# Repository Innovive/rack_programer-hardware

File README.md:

# rack_programer-hardware
Hardware tool for continuous integration and engineering testing for 3.5 racks

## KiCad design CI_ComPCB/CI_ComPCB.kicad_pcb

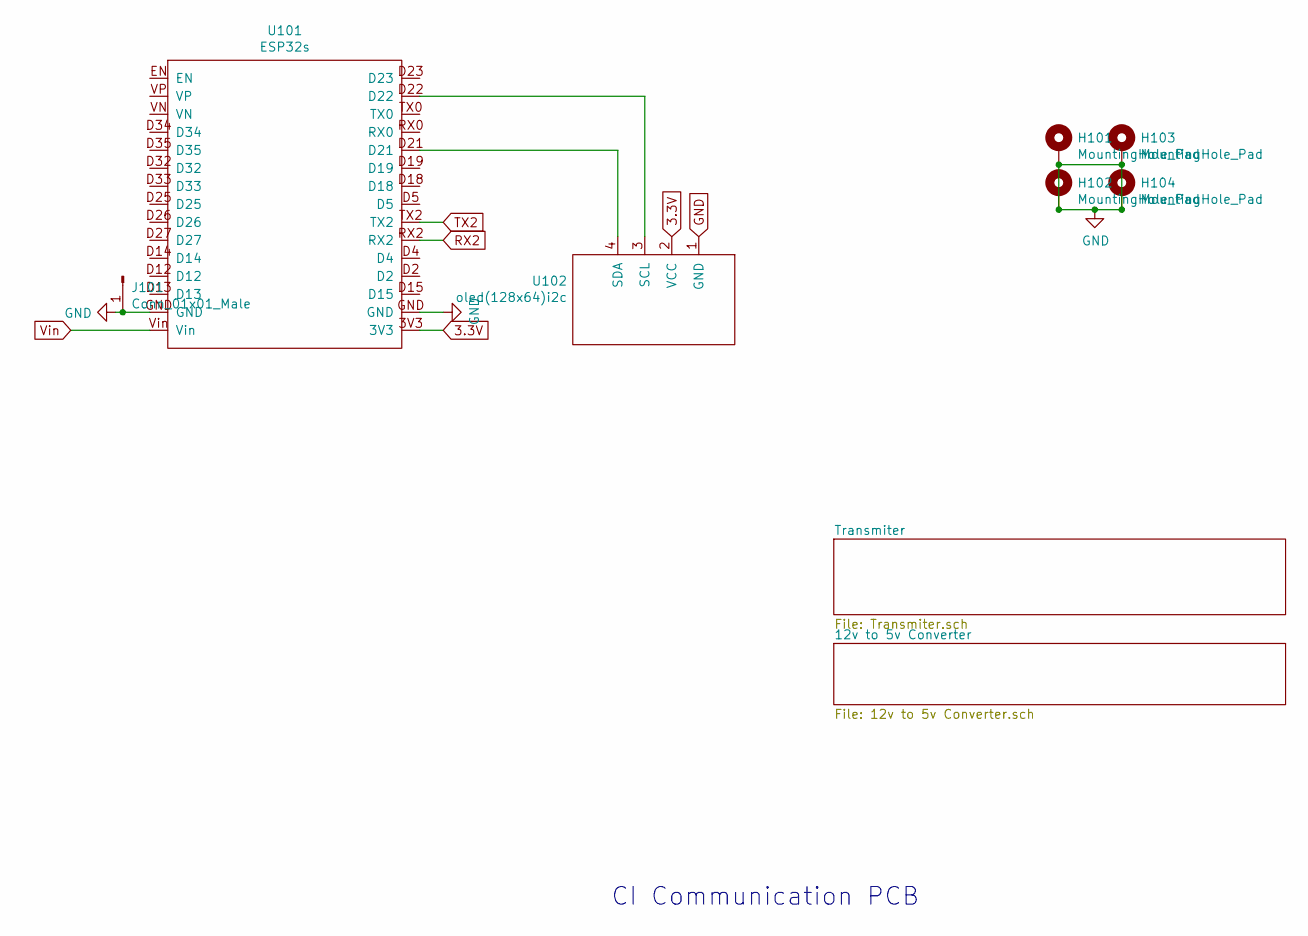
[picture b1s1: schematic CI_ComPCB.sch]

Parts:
H101, H102, H103, H104: MountingHole_Pad; MountingHole_3.2mm_M3_ISO7380_Pad_TopBottom
J101: Conn_01x01_Male; PinHeader_1x01_P2.54mm_Vertical
U101: ESP32s
U102: oled(128x64)i2c

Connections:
3.3V: U101.3V3, U102.2 (VCC); also elsewhere on the board
GND: H101.1, H102.1, H103.1, H104.1, J101.1, U101.GND, U102.1 (GND); also elsewhere on the board
unnamed: U101.D21, U102.4 (SDA)
unnamed: U101.D22, U102.3 (SCL)
RX2: U101.RX2; also elsewhere on the board
TX2: U101.TX2; also elsewhere on the board
Vin: U101.Vin; also elsewhere on the board

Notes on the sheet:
CI Communication PCB

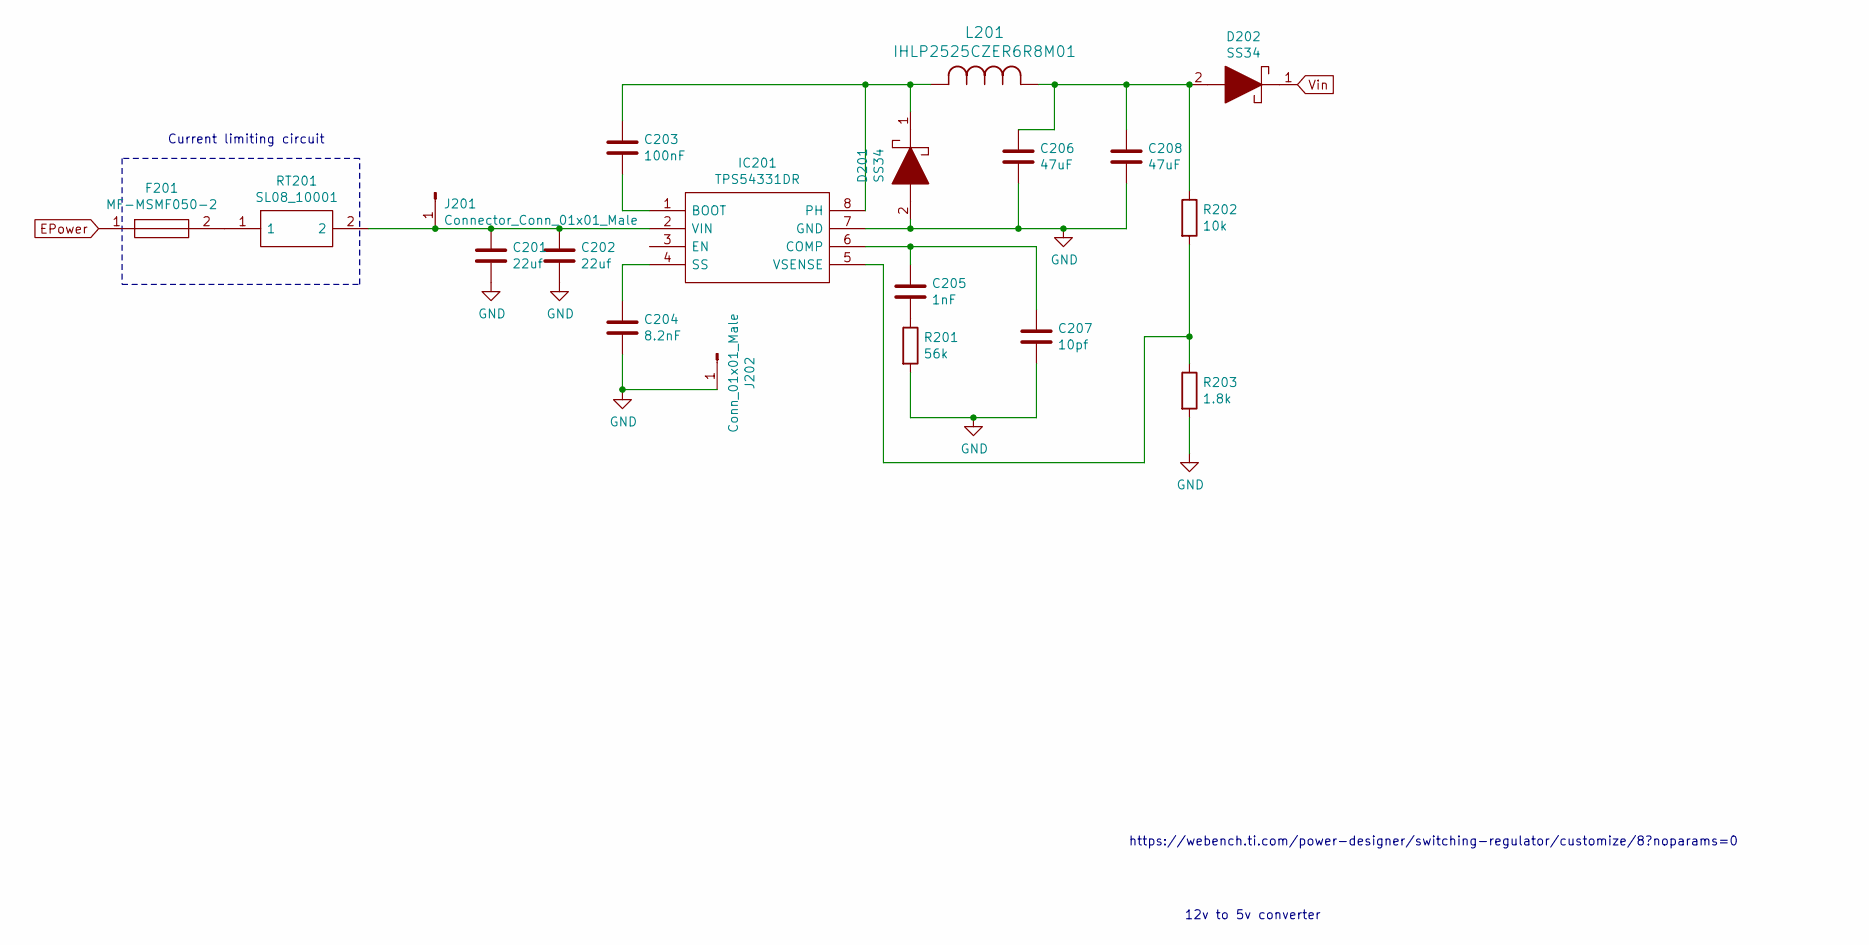
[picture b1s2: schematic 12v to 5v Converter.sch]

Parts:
C201, C202: 22uf; C_1206_3216Metric
C203: 100nF; C_0805_2012Metric
C204: 8.2nF; C_0603_1608Metric; JLCPCB C1032
C205: 1nF; C_0805_2012Metric
C206, C208: 47uF; C_0805_2012Metric
C207: 10pf; C_0805_2012Metric
D201, D202: SS34; DO-214AC; Mouser Part Number 512-SS34
F201: MF-MSMF050-2; FUSC4632X85N; Mouser Part Number 652-MF-MSMF050-2
IC201: TPS54331DR; SOIC127P600X175-8N; Mouser Part Number 595-TPS54331DR
J201: Connector_Conn_01x01_Male; PinHeader_1x01_P2.54mm_Vertical
J202: Conn_01x01_Male; PinHeader_1x01_P2.54mm_Vertical
L201: IHLP2525CZER6R8M01
R201: 56k; R_0805_2012Metric
R202: 10k; R_0805_2012Metric
R203: 1.8k; R_0805_2012Metric
RT201: SL08_10001; SL0810001; Mouser Part Number 995-SL0810001

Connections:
EPower: F201.1; also elsewhere on the board
GND: C201.2, C202.2, C204.2, C206.2, C207.2, C208.2, D201.2, IC201.7 (GND), J202.1, R201.2, R203.2; also elsewhere on the board
unnamed: C201.1, C202.1, IC201.2 (VIN), J201.1, RT201.2
unnamed: C203.1, D201.1, IC201.8 (PH), L201.2
unnamed: C203.2, IC201.1 (BOOT)
unnamed: C204.1, IC201.4 (SS)
unnamed: C205.1, C207.1, IC201.6 (COMP)
unnamed: C205.2, R201.1
unnamed: C206.1, C208.1, D202.2, L201.1, R202.1
unnamed: F201.2, RT201.1
unnamed: IC201.5 (VSENSE), R202.2, R203.1
Vin: D202.1; also elsewhere on the board

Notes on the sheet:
12v to 5v converter
https://webench.ti.com/power-designer/switching-regulator/customize/8?noparams=0
Current limiting circuit

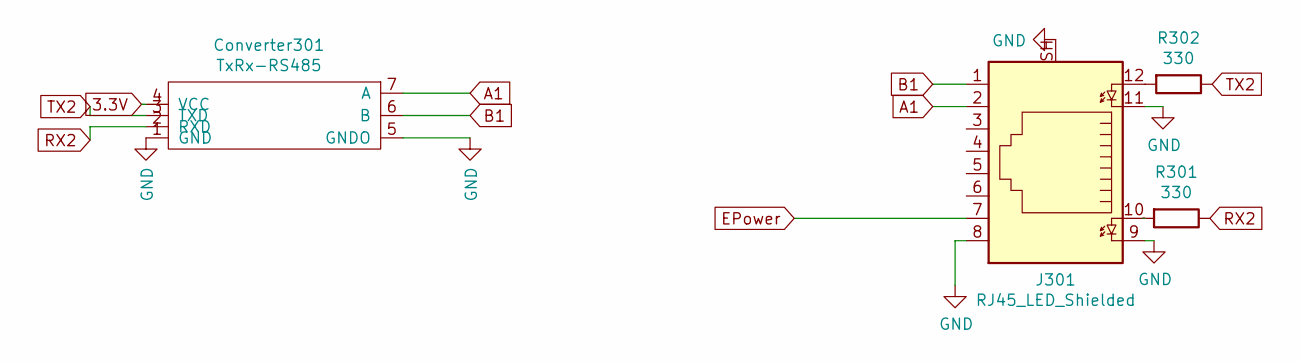
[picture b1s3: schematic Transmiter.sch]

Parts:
Converter301: TxRx-RS485; TXRX-AB
J301: RJ45_LED_Shielded; RJ45_Amphenol_RJHSE538X
R301, R302: 330; R_0805_2012Metric

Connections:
3.3V: Converter301.4 (VCC); also elsewhere on the board
A1: Converter301.7 (A), J301.2
B1: Converter301.6 (B), J301.1
EPower: J301.7; also elsewhere on the board
GND: Converter301.1 (GND), Converter301.5 (GNDO), J301.8, J301.9, J301.11, J301.SH; also elsewhere on the board
unnamed: J301.10, R301.2
unnamed: J301.12, R302.2
RX2: Converter301.2 (RXD), R301.1; also elsewhere on the board
TX2: Converter301.3 (TXD), R302.1; also elsewhere on the board

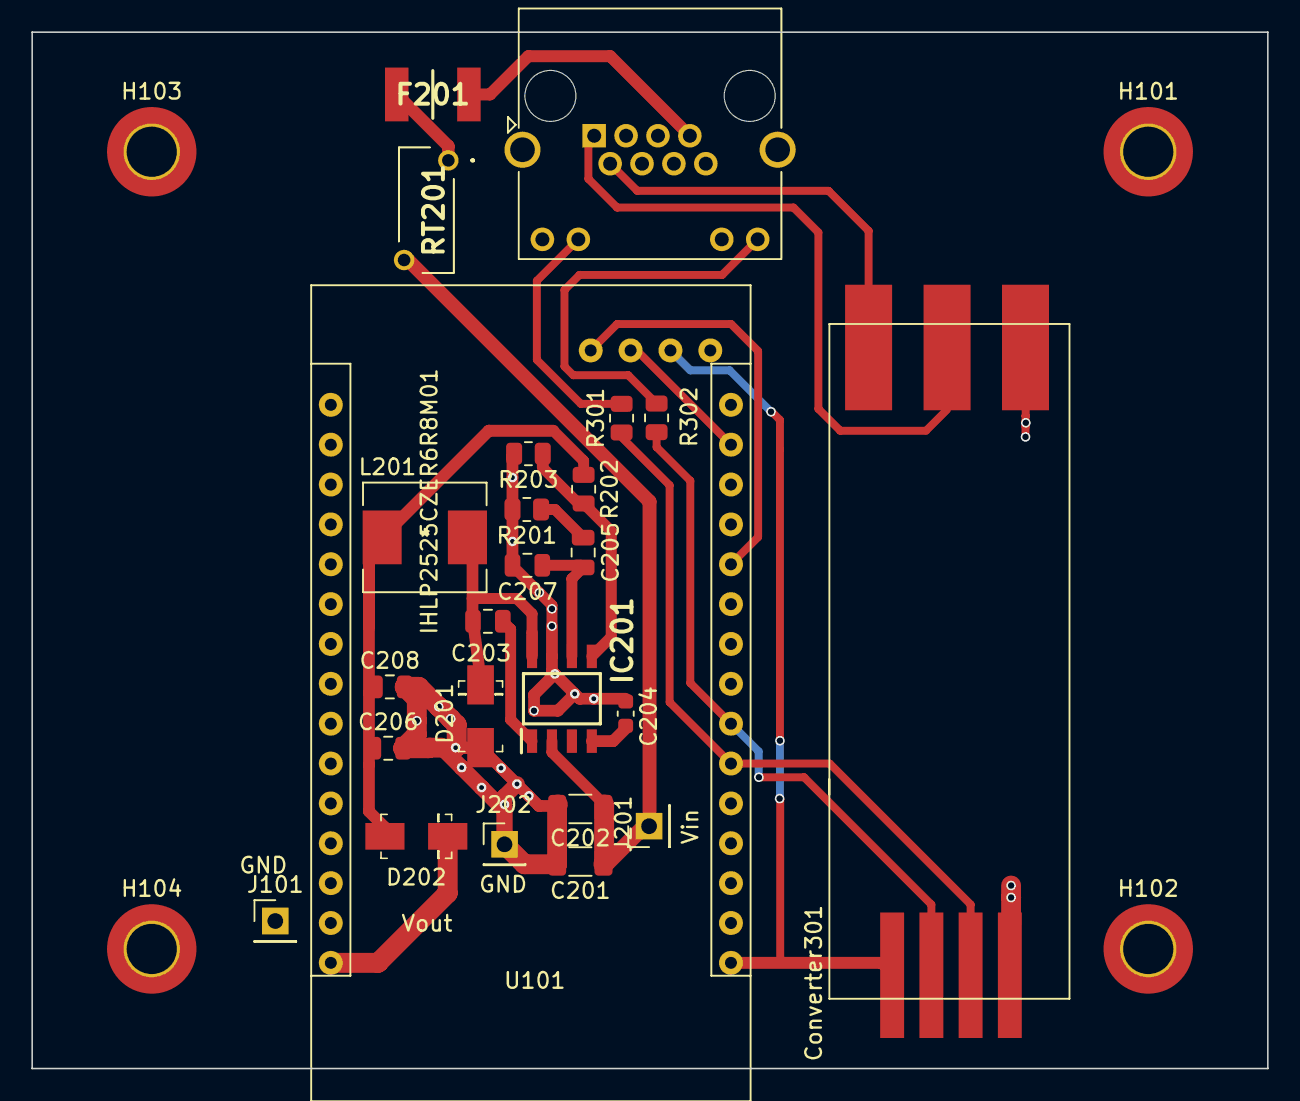
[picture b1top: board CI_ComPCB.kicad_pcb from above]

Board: 2 copper layers, 78.7 x 66.0 mm, 30 parts (1 on the bottom side), 21 nets.

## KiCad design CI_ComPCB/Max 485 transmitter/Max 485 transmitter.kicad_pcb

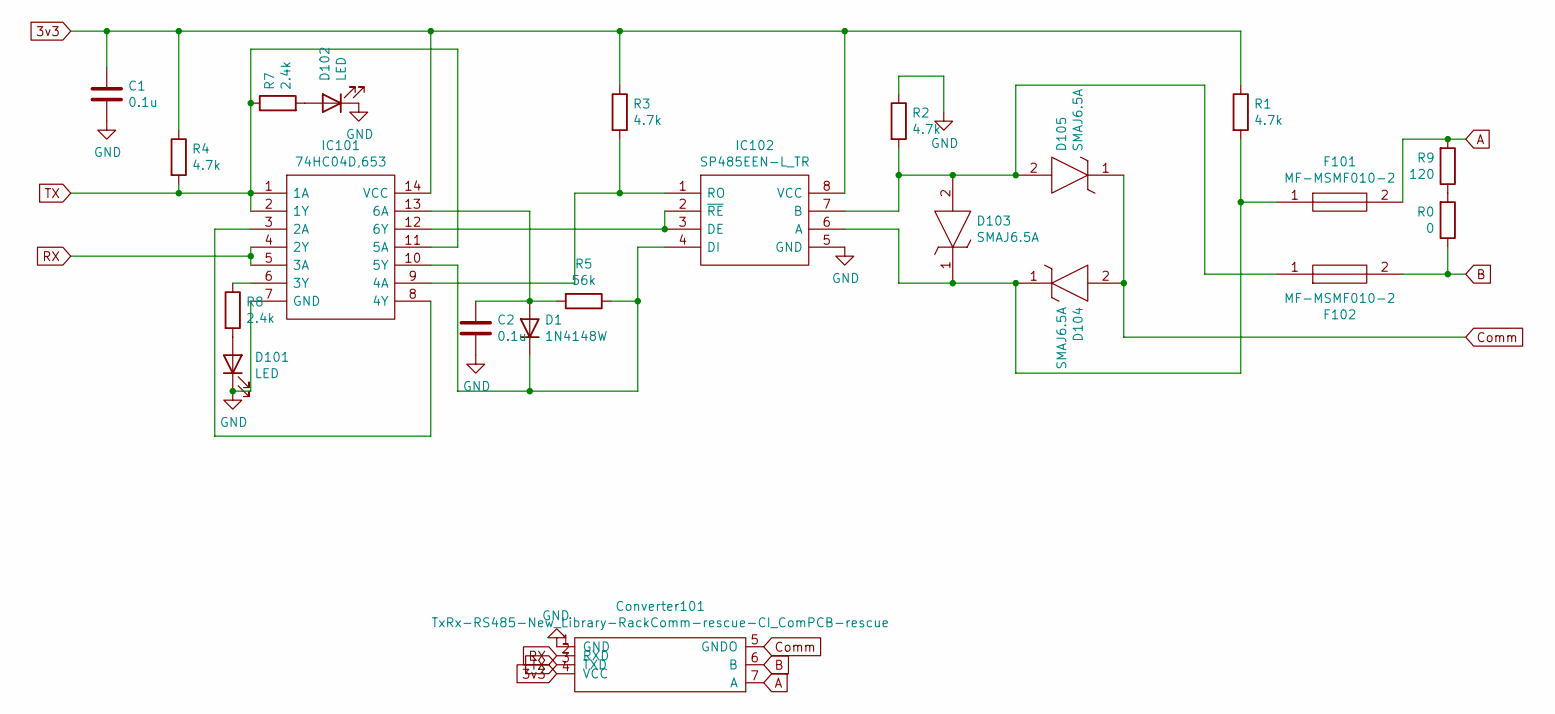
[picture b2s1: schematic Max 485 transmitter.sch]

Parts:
C1, C2: 0.1u; C_0402_1005Metric
Converter101: TxRx-RS485-New_Library-RackComm-rescue-CI_ComPCB-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; TXRX-AB
D1: 1N4148W; D_SOD-123
D101, D102: LED; LED_0603
D103, D104, D105: SMAJ6.5A; DIOM5026X229N; Mouser Part Number 576-SMAJ6.5A
F101, F102: MF-MSMF010-2; FUSC4632X110N; Mouser Part Number 652-MF-MSMF010-2
IC101: 74HC04D,653; SOIC127P600X175-14N; Mouser Part Number 771-74HC04D-T
IC102: SP485EEN-L_TR; SOIC127P600X175-8N; Mouser Part Number 701-SP485EEN-L/TR
R0: 0; R_0402_1005Metric
R1, R2, R3, R4: 4.7k; R_0402_1005Metric
R5: 56k; R_0402_1005Metric
R7, R8: 2.4k; R_0402_1005Metric
R9: 120; R_0402_1005Metric

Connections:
3v3: C1.1, Converter101.4 (VCC), IC101.14 (VCC), IC102.8 (VCC), R1.1, R3.1, R4.1
A: Converter101.7 (A), F101.2, R9.2
B: Converter101.6 (B), F102.2, R0.1
Comm: Converter101.5 (GNDO), D104.2, D105.1
GND: C1.2, C2.2, Converter101.1 (GND), D101.1 (K), D102.1 (K), IC101.7 (GND), IC102.5 (GND), R2.1
unnamed: C2.1, D1.2 (A), IC101.13 (6A), R5.2
unnamed: D1.1 (K), IC101.10 (5Y), IC102.4 (DI), R5.1
unnamed: D101.2 (A), R8.2
unnamed: D102.2 (A), R7.2
unnamed: D103.1, D104.1, F101.1, IC102.6 (A), R1.2
unnamed: D103.2, D105.2, F102.1, IC102.7 (B), R2.2
unnamed: IC101.3 (2A), IC101.8 (4Y)
unnamed: IC101.6 (3Y), R8.1
unnamed: IC101.9 (4A), IC102.1 (RO), R3.2
unnamed: IC101.12 (6Y), IC102.2 (~RE), IC102.3 (DE)
unnamed: R0.2, R9.1
RX: Converter101.2 (RXD), IC101.4 (2Y), IC101.5 (3A)
TX: Converter101.3 (TXD), IC101.1 (1A), IC101.2 (1Y), IC101.11 (5A), R4.2, R7.1

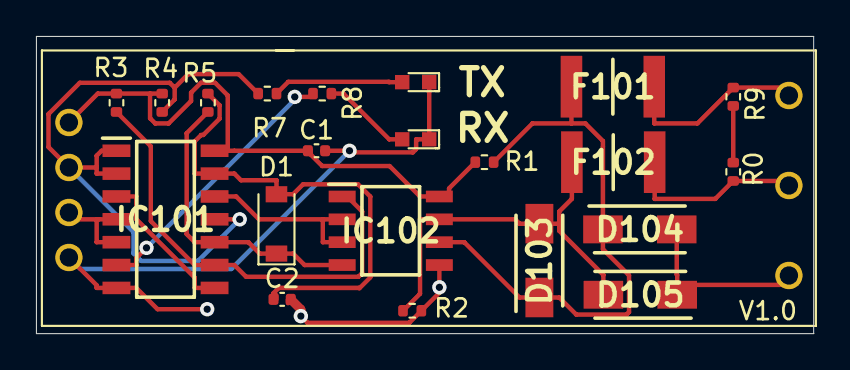
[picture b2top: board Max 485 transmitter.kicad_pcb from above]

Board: 2 copper layers, 43.2 x 16.5 mm, 22 parts (0 on the bottom side), 18 nets.

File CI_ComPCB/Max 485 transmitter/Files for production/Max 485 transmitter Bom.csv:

Value,Designator,Footprint,JLPCB Part#
0.1u,C1,Capacitor_SMD:C_0201_0603Metric,C1525
0.1u,C2,Capacitor_SMD:C_0201_0603Metric,C1525
1N4148W,D1,Diode_SMD:D_SOD-123,C81598
LED,D101,digikey-footprints:LED_0603,C72038
LED,D102,digikey-footprints:LED_0603,C72038
SMAJ6.5A,D103,SamacSys_Parts:DIOM5026X229N,C283910
SMAJ6.5A,D104,SamacSys_Parts:DIOM5026X229N,C283910
SMAJ6.5A,D105,SamacSys_Parts:DIOM5026X229N,C283910
MF-MSMF010-2,F101,SamacSys_Parts:FUSC4632X110N,C12430
MF-MSMF010-2,F102,SamacSys_Parts:FUSC4632X110N,C12430
"74HC04D,653",IC101,SamacSys_Parts:SOIC127P600X175-14N,C5590
SP485EEN-L_TR,IC102,SamacSys_Parts:SOIC127P600X175-8N,C6855
4.7k,R1,Resistor_SMD:R_0402_1005Metric,C25900
4.7k,R2,Resistor_SMD:R_0402_1005Metric,C25900
4.7k,R3,Resistor_SMD:R_0402_1005Metric,C25900
4.7k,R4,Resistor_SMD:R_0402_1005Metric,C25901
56k,R5,Resistor_SMD:R_0402_1005Metric,C25796
2.4k,R7,Resistor_SMD:R_0402_1005Metric,C25882
2.4k,R8,Resistor_SMD:R_0402_1005Metric,C25882
120,R9,Resistor_SMD:R_0402_1005Metric,C25079

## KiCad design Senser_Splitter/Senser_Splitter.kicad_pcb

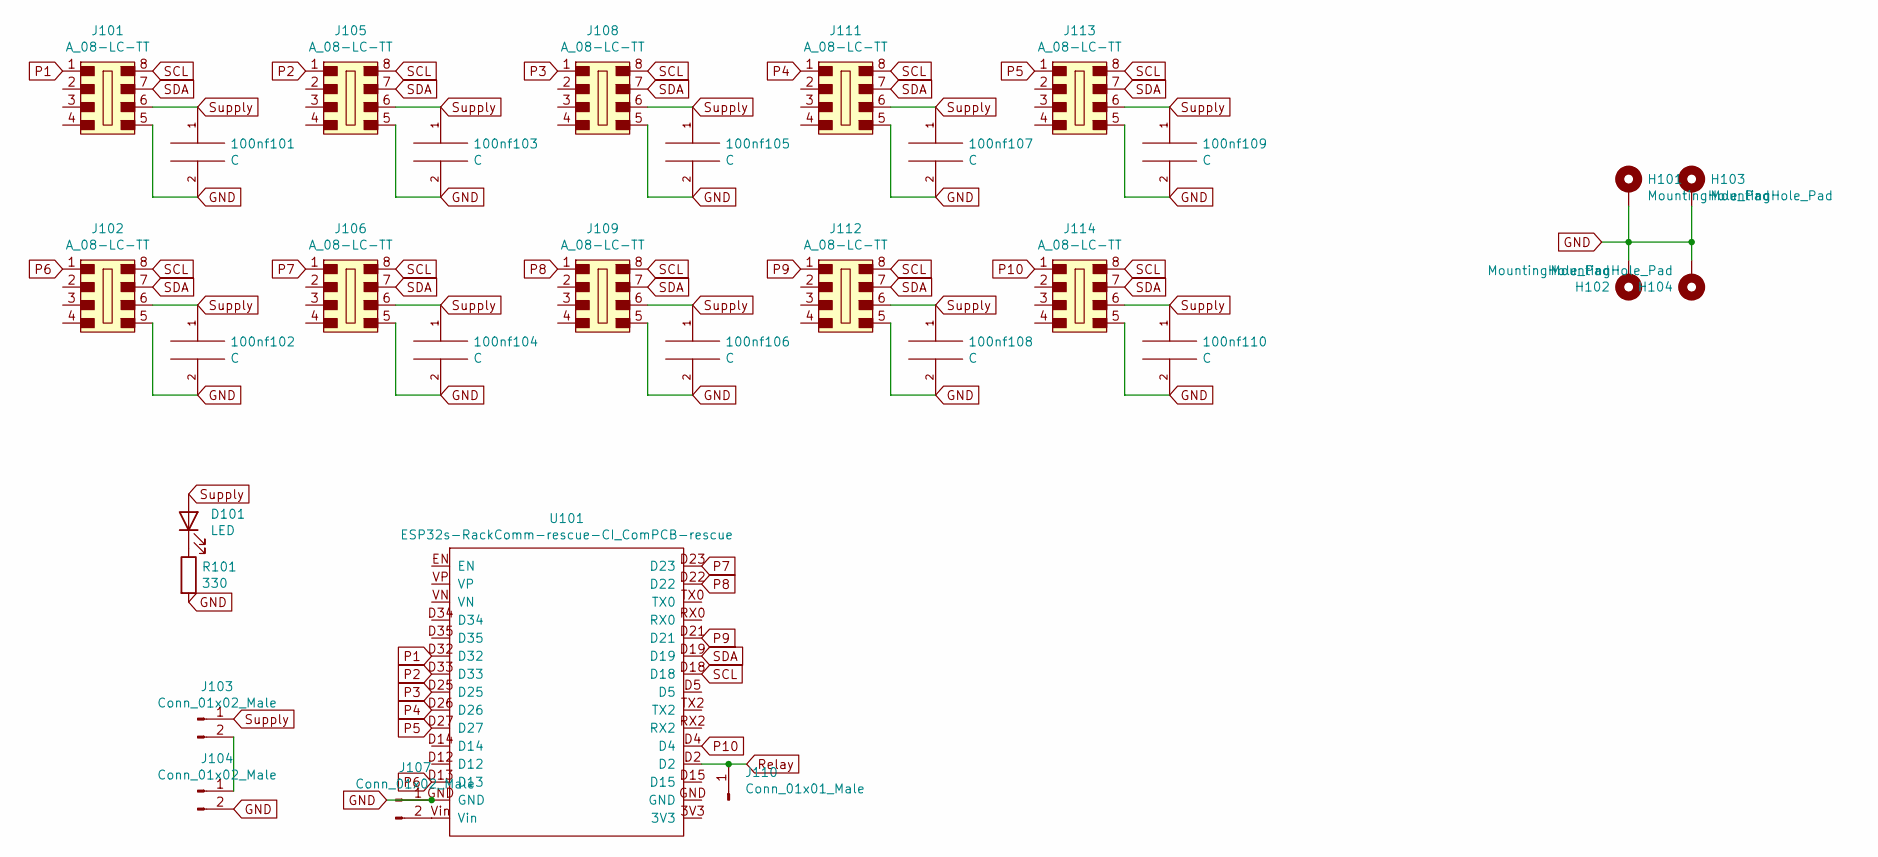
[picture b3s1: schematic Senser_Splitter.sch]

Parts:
100nf101, 100nf102, 100nf103, 100nf104, 100nf105, 100nf106, 100nf107, 100nf108, 100nf109, 100nf110: C; C_1206_3216Metric_Pad1.33x1.80mm_HandSolder
D101: LED; LED_D3.0mm_Clear
H101, H102, H103, H104: MountingHole_Pad; MountingHole_2.2mm_M2_DIN965_Pad_TopBottom
J101, J102, J105, J106, J108, J109, J111, J112, J113, J114: A_08-LC-TT; SOCKET_DIP-8_7.62mm_Conn; MPN A 08-LC-TT; Digi-Key_PN AE9986-ND
J103, J104, J107: Conn_01x02_Male; PinHeader_1x02_P2.54mm_Vertical
J110: Conn_01x01_Male; PinHeader_1x01_P2.54mm_Vertical
R101: 330; R_Axial_DIN0204_L3.6mm_D1.6mm_P5.08mm_Horizontal
U101: ESP32s-RackComm-rescue-CI_ComPCB-rescue; ESP32s

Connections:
GND: 100nf101.2, 100nf102.2, 100nf103.2, 100nf104.2, 100nf105.2, 100nf106.2, 100nf107.2, 100nf108.2, 100nf109.2, 100nf110.2, H101.1, H102.1, H103.1, H104.1, J101.5, J102.5, J104.2, J105.5, J106.5, J107.1, J108.5, J109.5, J111.5, J112.5, J113.5, J114.5, R101.2, U101.GND
unnamed: D101.1 (K), R101.1
unnamed: J103.2, J104.1
unnamed: J107.2, U101.Vin
P1: J101.1, U101.D32
P2: J105.1, U101.D33
P3: J108.1, U101.D25
P4: J111.1, U101.D26
P5: J113.1, U101.D27
P6: J102.1, U101.D13
P7: J106.1, U101.D23
P8: J109.1, U101.D22
P9: J112.1, U101.D21
P10: J114.1, U101.D4
Relay: J110.1, U101.D2
SCL: J101.8, J102.8, J105.8, J106.8, J108.8, J109.8, J111.8, J112.8, J113.8, J114.8, U101.D18
SDA: J101.7, J102.7, J105.7, J106.7, J108.7, J109.7, J111.7, J112.7, J113.7, J114.7, U101.D19
Supply: 100nf101.1, 100nf102.1, 100nf103.1, 100nf104.1, 100nf105.1, 100nf106.1, 100nf107.1, 100nf108.1, 100nf109.1, 100nf110.1, D101.2 (A), J101.6, J102.6, J103.1, J105.6, J106.6, J108.6, J109.6, J111.6, J112.6, J113.6, J114.6

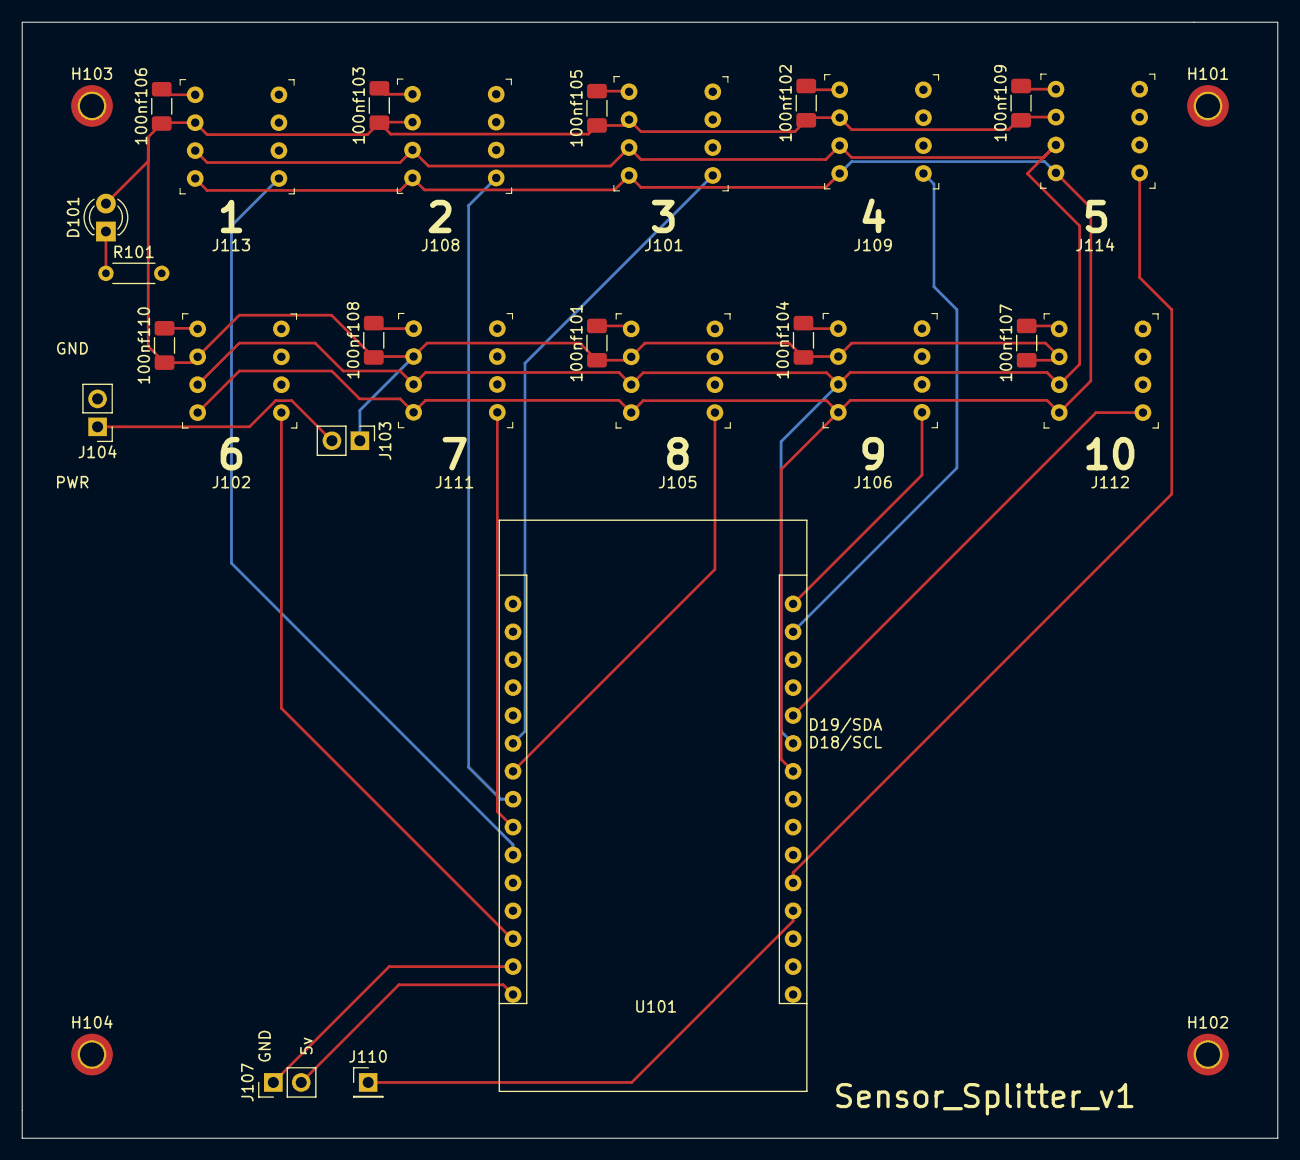
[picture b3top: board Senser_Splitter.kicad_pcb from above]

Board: 2 copper layers, 114.3 x 101.6 mm, 31 parts (0 on the bottom side), 18 nets.

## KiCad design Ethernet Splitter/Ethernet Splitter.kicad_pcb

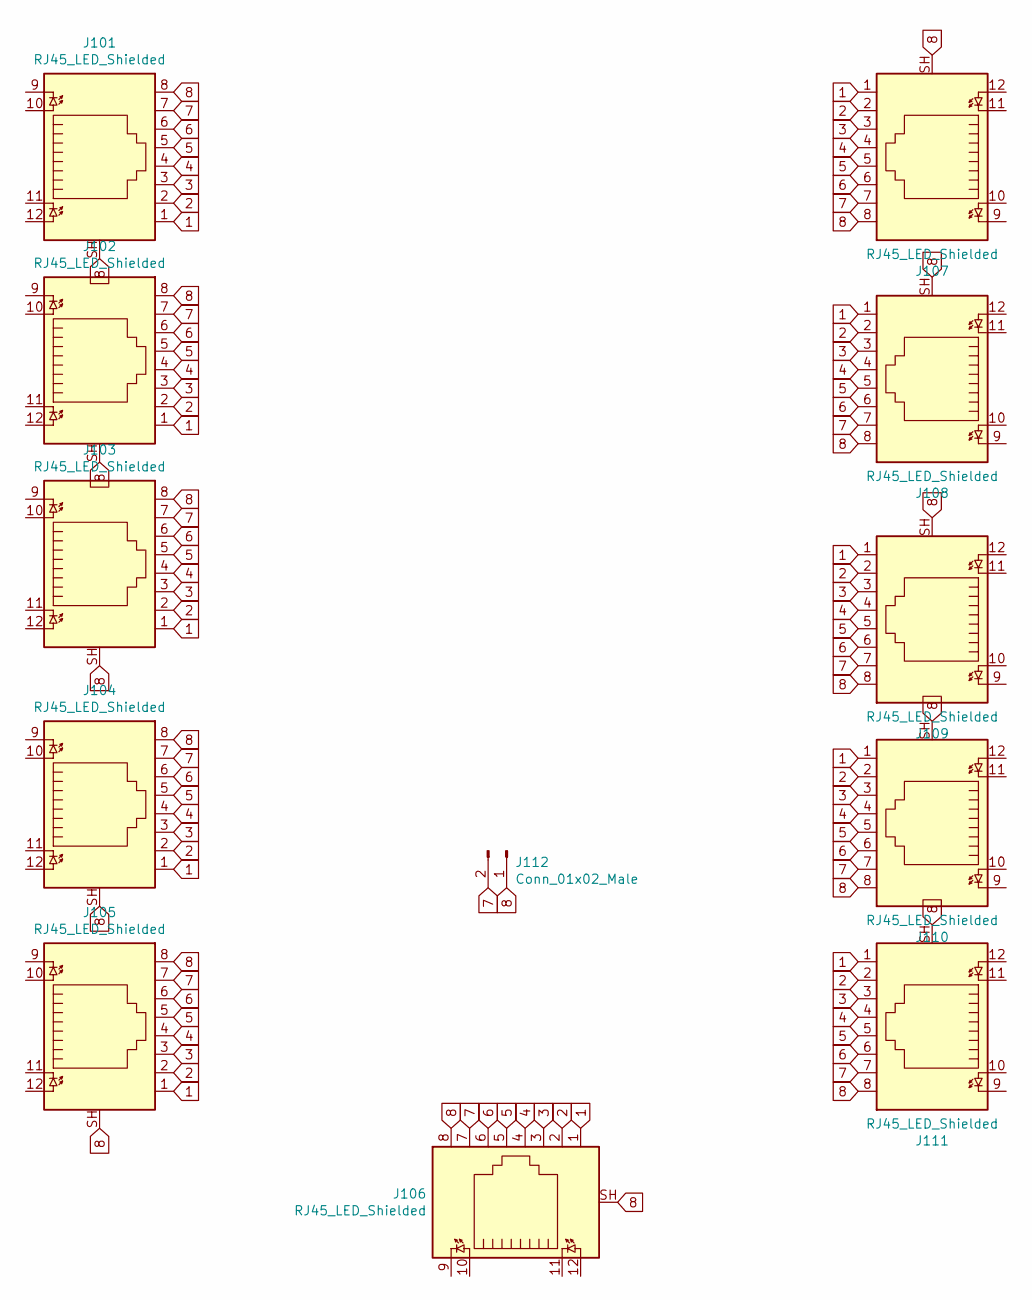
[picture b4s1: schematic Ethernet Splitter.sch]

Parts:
J101, J102, J103, J104, J105, J106, J107, J108, J109, J110, J111: RJ45_LED_Shielded; RJ45_Amphenol_RJHSE538X
J112: Conn_01x02_Male; PinHeader_1x02_P2.54mm_Vertical

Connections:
1: J101.1, J102.1, J103.1, J104.1, J105.1, J106.1, J107.1, J108.1, J109.1, J110.1, J111.1
2: J101.2, J102.2, J103.2, J104.2, J105.2, J106.2, J107.2, J108.2, J109.2, J110.2, J111.2
3: J101.3, J102.3, J103.3, J104.3, J105.3, J106.3, J107.3, J108.3, J109.3, J110.3, J111.3
4: J101.4, J102.4, J103.4, J104.4, J105.4, J106.4, J107.4, J108.4, J109.4, J110.4, J111.4
5: J101.5, J102.5, J103.5, J104.5, J105.5, J106.5, J107.5, J108.5, J109.5, J110.5, J111.5
6: J101.6, J102.6, J103.6, J104.6, J105.6, J106.6, J107.6, J108.6, J109.6, J110.6, J111.6
7: J101.7, J102.7, J103.7, J104.7, J105.7, J106.7, J107.7, J108.7, J109.7, J110.7, J111.7, J112.2
8: J101.8, J101.SH, J102.8, J102.SH, J103.8, J103.SH, J104.8, J104.SH, J105.8, J105.SH, J106.8, J106.SH, J107.8, J107.SH, J108.8, J108.SH, J109.8, J109.SH, J110.8, J110.SH, J111.8, J111.SH, J112.1

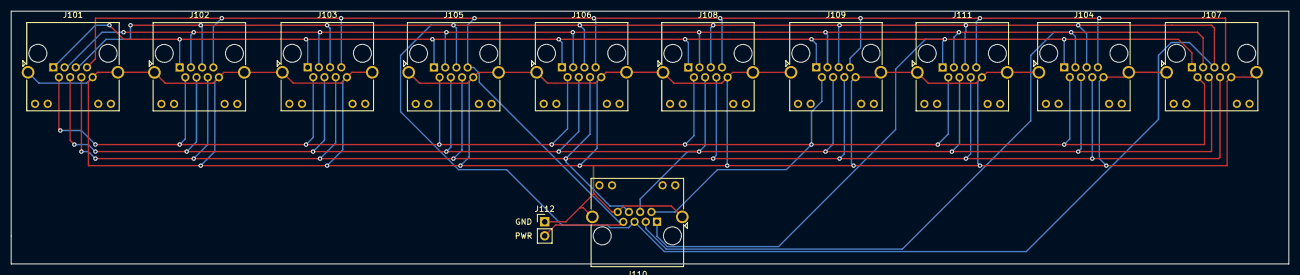
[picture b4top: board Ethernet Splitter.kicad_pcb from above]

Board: 2 copper layers, 231.1 x 45.7 mm, 12 parts (0 on the bottom side), 8 nets.

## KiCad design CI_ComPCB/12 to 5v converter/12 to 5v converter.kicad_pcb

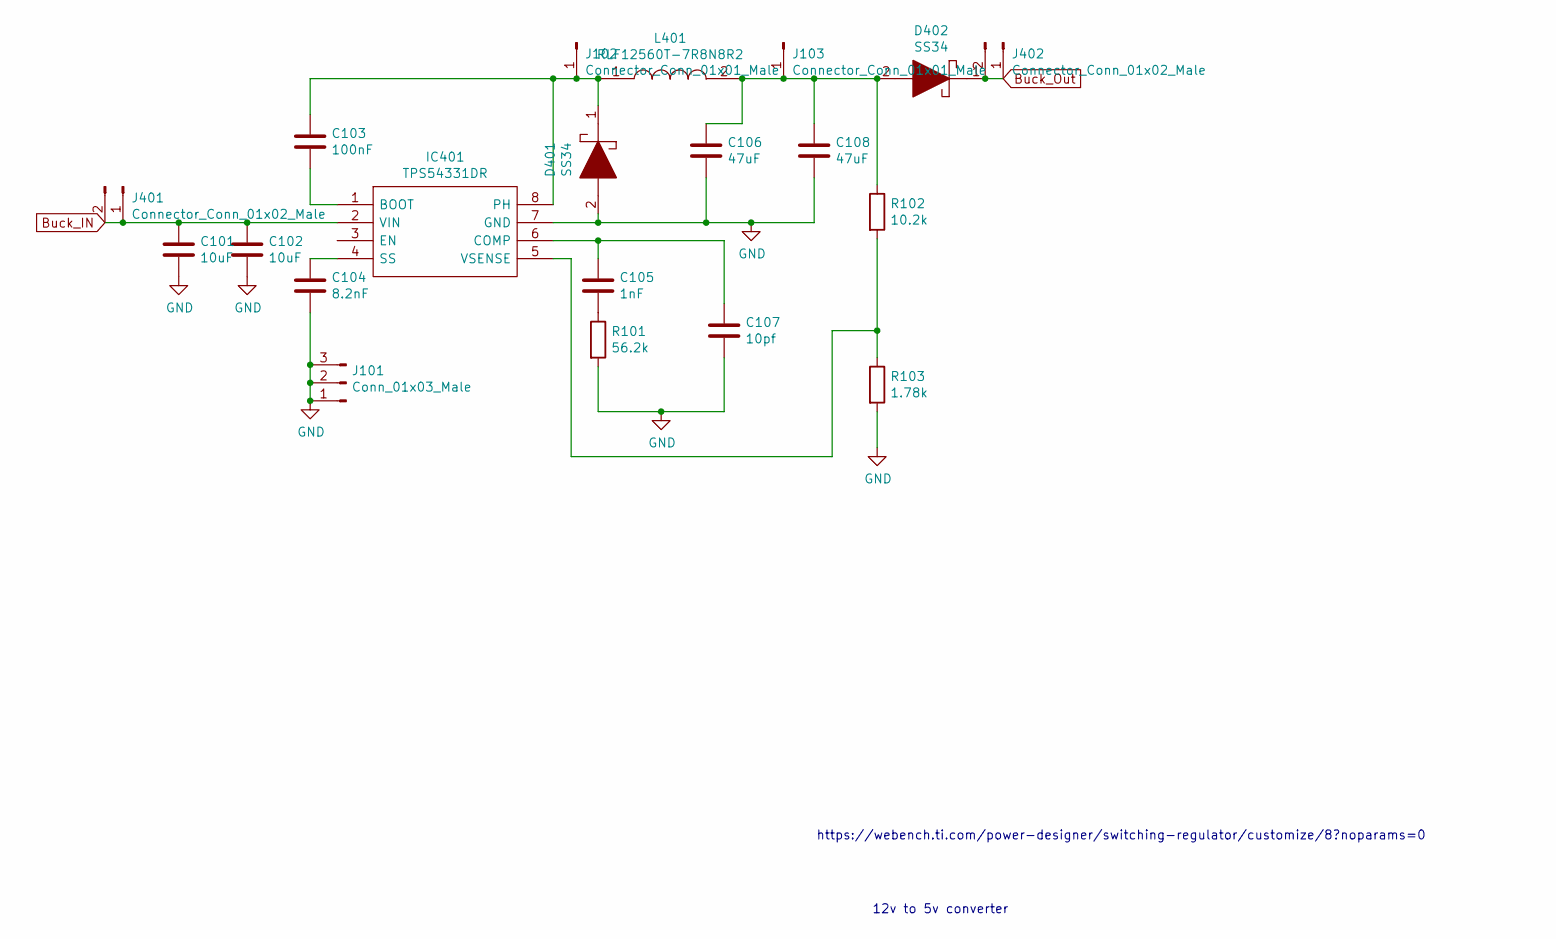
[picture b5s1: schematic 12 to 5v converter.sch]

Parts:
C101, C102: 10uF; C_0805_2012Metric
C103: 100nF; C_0805_2012Metric
C104: 8.2nF; C_0805_2012Metric; JLCPCB C1032
C105: 1nF; C_0805_2012Metric
C106, C108: 47uF; C_0805_2012Metric
C107: 10pf; C_0805_2012Metric
D401, D402: SS34; DO-214AC; Mouser Part Number 512-SS34
IC401: TPS54331DR; SOIC127P600X175-8N; Mouser Part Number 595-TPS54331DR
J101: Conn_01x03_Male; PinHeader_1x03_P2.54mm_Vertical
J102, J103: Connector_Conn_01x01_Male; PinHeader_1x01_P2.54mm_Vertical
J401, J402: Connector_Conn_01x02_Male; PinHeader_1x02_P2.54mm_Vertical
L401: RLF12560T-7R8N8R2; INDPM128125X600N; Mouser Part Number 810-RLF12560T-7R8N
R101: 56.2k; R_0805_2012Metric
R102: 10.2k; R_0805_2012Metric
R103: 1.78k; R_0805_2012Metric

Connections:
Buck_IN: C101.1, C102.1, IC401.2 (VIN), J401.1, J401.2
Buck_Out: D402.1, J402.1, J402.2
GND: C101.2, C102.2, C104.2, C106.2, C107.2, C108.2, D401.2, IC401.7 (GND), J101.1, J101.2, J101.3, R101.2, R103.2
unnamed: C103.1, D401.1, IC401.8 (PH), J102.1, L401.1
unnamed: C103.2, IC401.1 (BOOT)
unnamed: C104.1, IC401.4 (SS)
unnamed: C105.1, C107.1, IC401.6 (COMP)
unnamed: C105.2, R101.1
unnamed: C106.1, C108.1, D402.2, J103.1, L401.2, R102.1
unnamed: IC401.5 (VSENSE), R102.2, R103.1

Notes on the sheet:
12v to 5v converter
https://webench.ti.com/power-designer/switching-regulator/customize/8?noparams=0

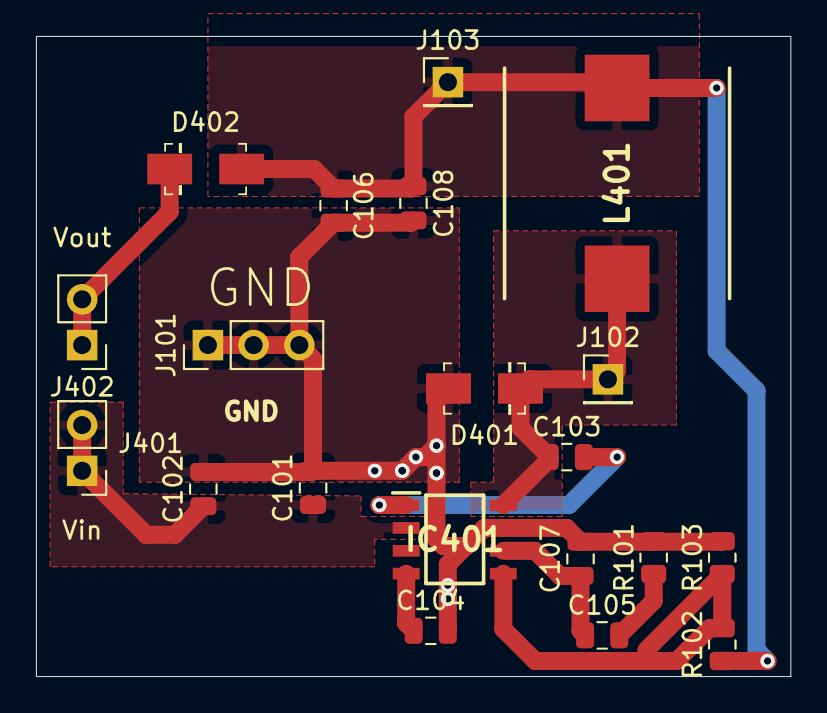
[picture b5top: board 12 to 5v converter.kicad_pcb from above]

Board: 2 copper layers, 41.9 x 35.6 mm, 20 parts (0 on the bottom side), 10 nets.

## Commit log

2021-08-18 Started new project for CI pcb
2021-08-18 Moved doc
2021-08-19 First PCB
    First PCB Printed with minor alterations
2021-08-20 Rough V1
2021-08-24 V1 w/ no Battery
2021-08-24 V1 w/ no Battery
    upgrade from first draft fixing issues #5 #20 #15 #12 #11 #6
2021-08-25 PCB Library upload
2021-08-25 V1 documentation and datasheets
2021-08-25 V1.1 working progress
    Implemented further documentation
    New boost converter for the battery
    power switches
    Led indicator
    removed unnecessary elements
2021-08-26 V1.1 in development
    Implemented sheets
    Added correct switches
    Completed boost converter
    REQUIRED before build:
    PCB layout
    Component matching with PCB maker
2021-08-27 V1.1 in progress
    Completed Bom and schematic
    still need to add routs and PCB layout
2021-08-28 temp
2021-08-28 V1.1 Rough
    Almost complete
    needs silk screen annotations then will be ready to have printed
2021-08-30 V1.1 Check
    Ready to print after final checks and adjustments
2021-08-30 V1.1 board
    Board is ready to print
2021-08-30 V1 Complete
2021-08-30 Adjusted git ignore to allow .csv
2021-08-30 Added bom file
2021-08-30 gerber files added
2021-08-31 V1.1 Changed Diode for reprint
2021-09-02 V1.2 Beginning
    Created transmitter module
2021-09-03 Transmitter print
2021-09-07 switch
2021-09-08 transmitter update
2021-09-17 converters debug
2021-09-17 documentation
2021-10-29 Ready to Build
2021-12-14 eSplitter
2021-12-14 stuff
2022-01-12 Production1
2022-01-13 print
2022-02-04 Sensor_SplitterPrint
2022-02-04 Move to Sub Folder
    Moved unrelated projects to a different repository called innovive Sub Projects
2022-03-18 New setup
2022-03-31 Small change on rs485
2022-04-30 prilim pcb finished
2022-05-03 temp2
2022-05-03 temp3

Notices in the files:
parts and their libraries:
Copyright 2021 Accelerated Designs. All rights reserved.
